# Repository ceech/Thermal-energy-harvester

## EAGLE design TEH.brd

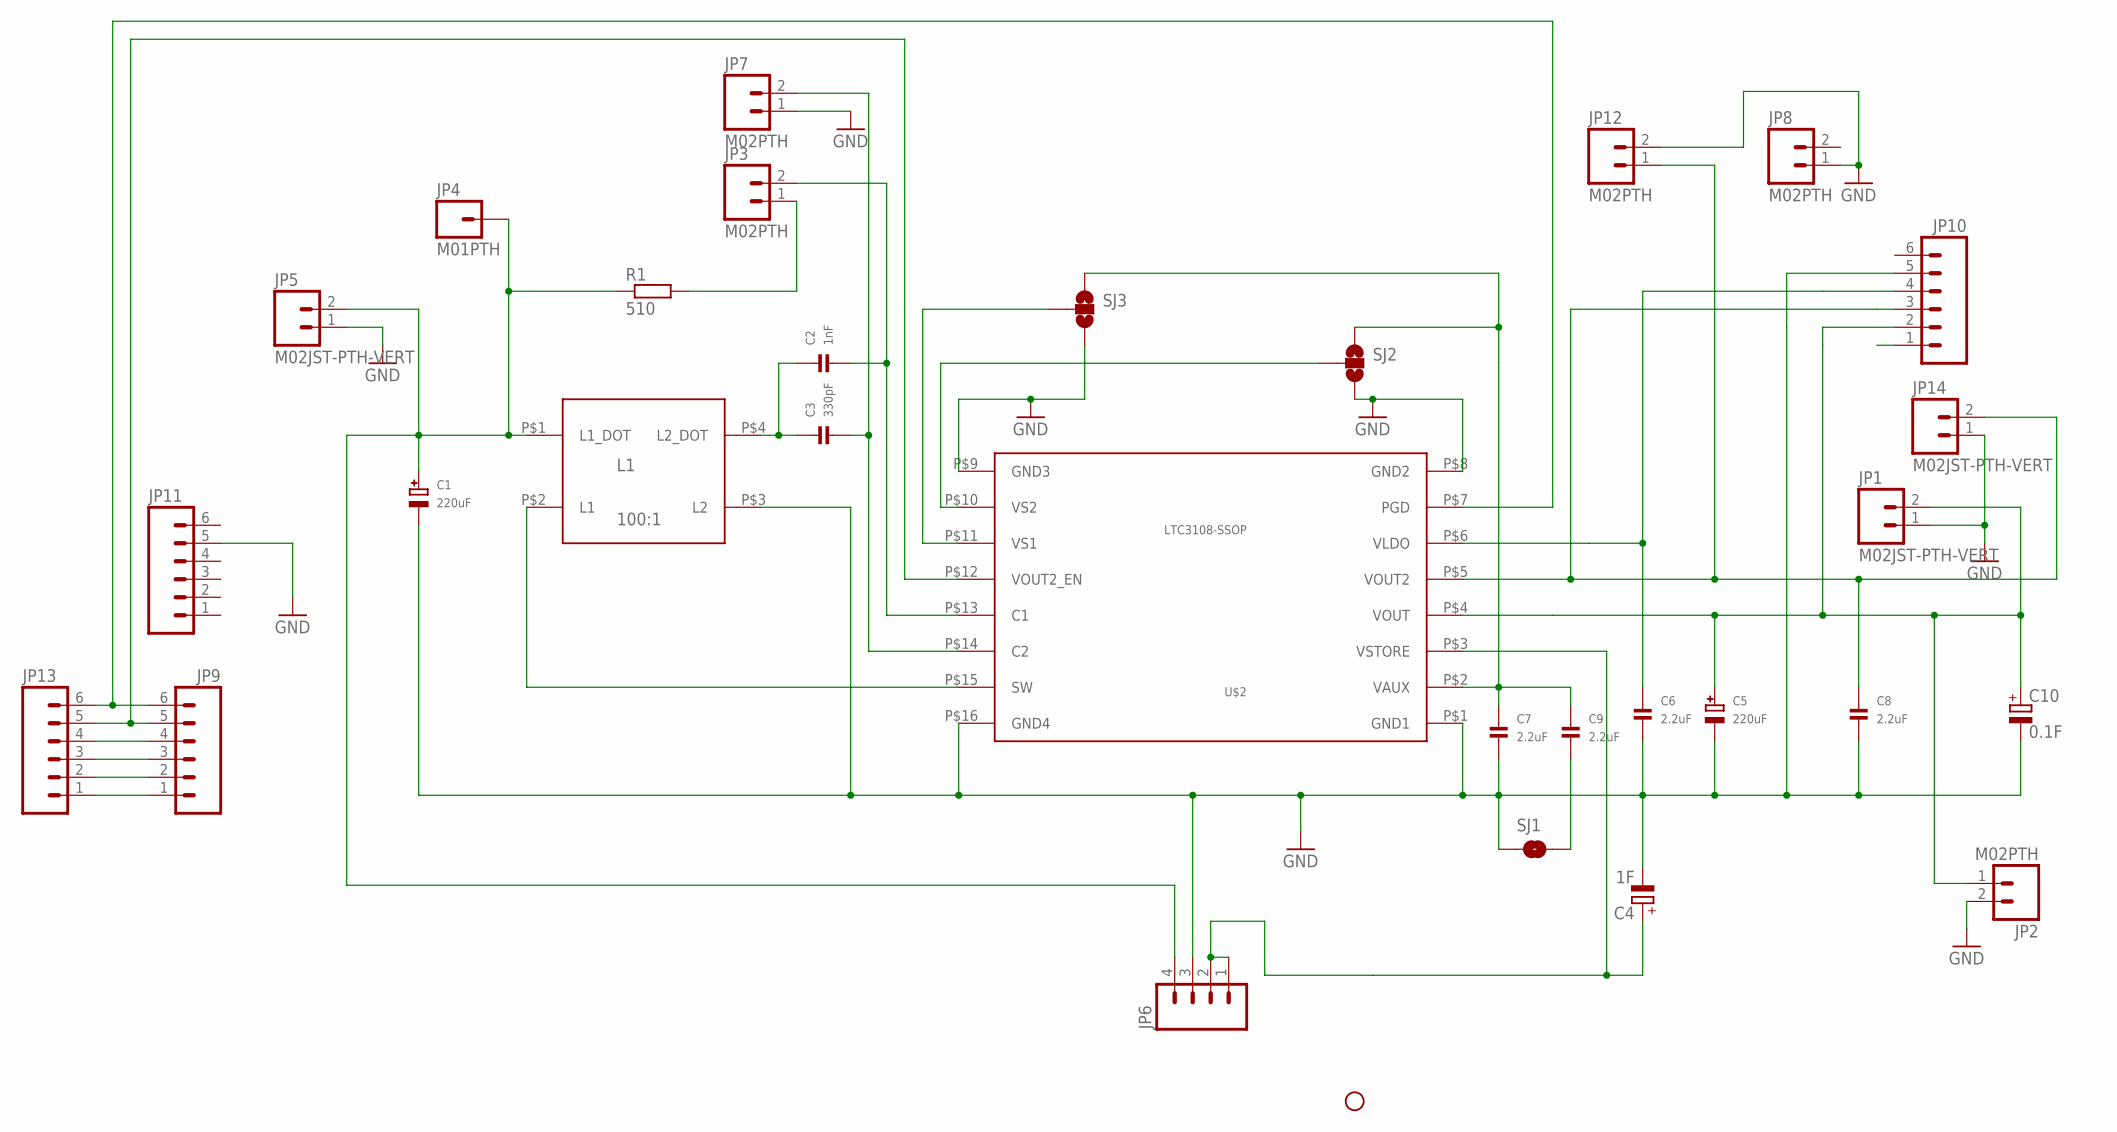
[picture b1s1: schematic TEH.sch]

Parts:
C1, C5: 220uF; EIA7343-31/D-R
C2: 1nF; 0805
C3: 330pF; 0805
C4: 1F; E5-13
C6, C7, C8, C9: 2.2uF; 0805
C10: 0.1F; E5-13
JP1, JP5, JP14: M02JST-PTH-VERT; JST-2-PTH-VERT
JP2, JP3, JP7, JP8, JP12: M02PTH; 1X02
JP4: M01PTH; 1X01
JP6: M04PTH; 1X04
JP9, JP10, JP11, JP13: M06NO_SILK; 1X06_NO_SILK
L1: 100:1; COILCRAFT_LPR6235
R1: 510; R0805
SJ1: JUMPER-PAD-2-NOYES_SILK; PAD-JUMPER-2-NO_YES_SILK
SJ2, SJ3: SOLDERJUMPER_2WAYT; SJ_2
STANDOFF2: STAND-OFFTIGHT; STAND-OFF-TIGHT
U$2: LTC3108-SSOP; SSOP-GN-16

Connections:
GND: C1.-, C4.-, C5.-, C6.2, C7.2, C8.2, C10.-, JP1.1, JP2.2, JP5.1, JP6.3, JP7.1, JP8.1, JP10.5, JP11.5, JP12.2, JP14.1, L1.P$3 (L2), SJ1.1, SJ2.3, SJ3.3, U$2.P$1 (GND1), U$2.P$8 (GND2), U$2.P$9 (GND3), U$2.P$16 (GND4)
unnamed: C1.+, JP4.1, JP5.2, JP6.4, L1.P$1 (L1_DOT), R1.1
unnamed: L1.P$2 (L1), U$2.P$15 (SW)
unnamed: C3.2, JP7.2, U$2.P$14 (C2)
unnamed: C5.+, C10.+, JP1.2, JP2.1, JP10.2, U$2.P$4 (VOUT)
unnamed: C2.1, C3.1, L1.P$4 (L2_DOT)
unnamed: C7.1, C9.1, SJ2.1, SJ3.1, U$2.P$2 (VAUX)
unnamed: C4.+, JP6.1, JP6.2, U$2.P$3 (VSTORE)
unnamed: JP9.6, JP13.6, U$2.P$7 (PGD)
unnamed: SJ3.2, U$2.P$11 (VS1)
unnamed: C6.1, JP10.4, U$2.P$6 (VLDO)
unnamed: JP9.5, JP13.5, U$2.P$12 (VOUT2_EN)
unnamed: C8.1, JP10.3, JP12.1, JP14.2, U$2.P$5 (VOUT2)
unnamed: SJ2.2, U$2.P$10 (VS2)
unnamed: C9.2, SJ1.2
unnamed: C2.2, JP3.2, U$2.P$13 (C1)
unnamed: JP3.1, R1.2
unnamed: JP9.4, JP13.4
unnamed: JP9.3, JP13.3
unnamed: JP9.2, JP13.2
unnamed: JP9.1, JP13.1

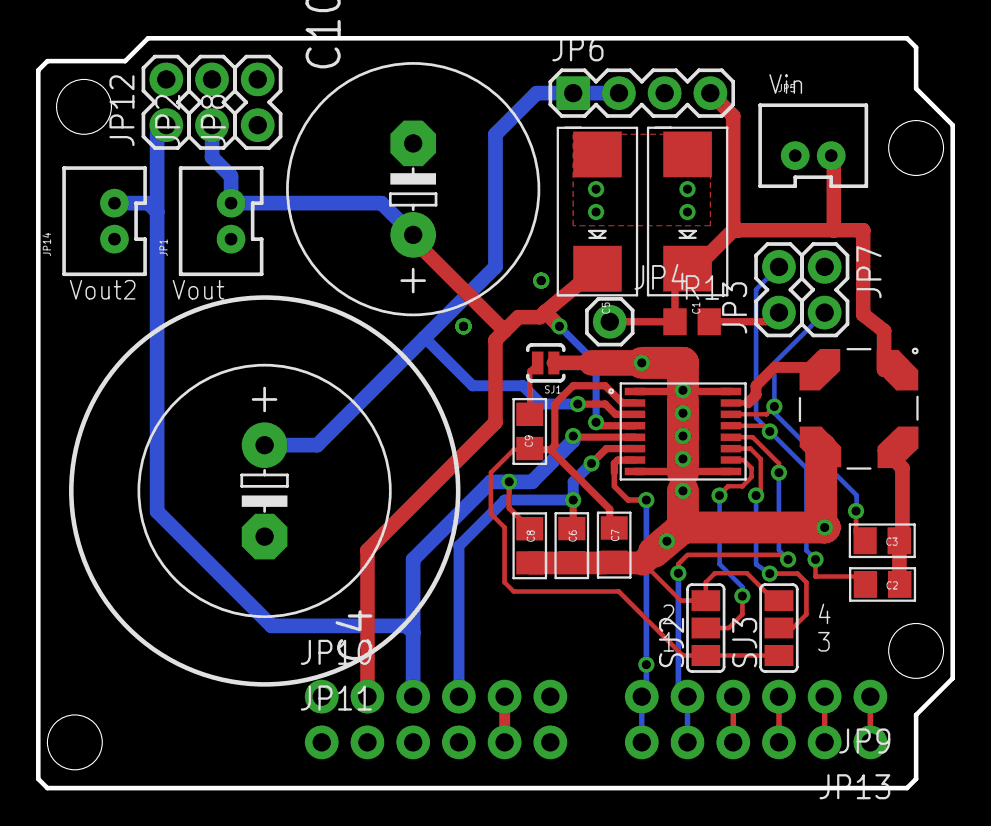
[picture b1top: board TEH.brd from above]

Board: 2 copper layers, 50.8 x 41.7 mm, 34 parts (0 on the bottom side), 21 nets.

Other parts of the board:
STANDOFF1, STANDOFF3, STANDOFF4: STAND-OFF; STAND-OFF-TIGHT

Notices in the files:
parts and their libraries:
SparkFun-Connectors: Licensing: Creative Commons ShareAlike 4.0 International - https://creativecommons.org/licenses/by-sa/4.0
